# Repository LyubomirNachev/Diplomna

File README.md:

# Diplomna
Проектиране на сензорна IoT мрежа, използваща протокола Thread.

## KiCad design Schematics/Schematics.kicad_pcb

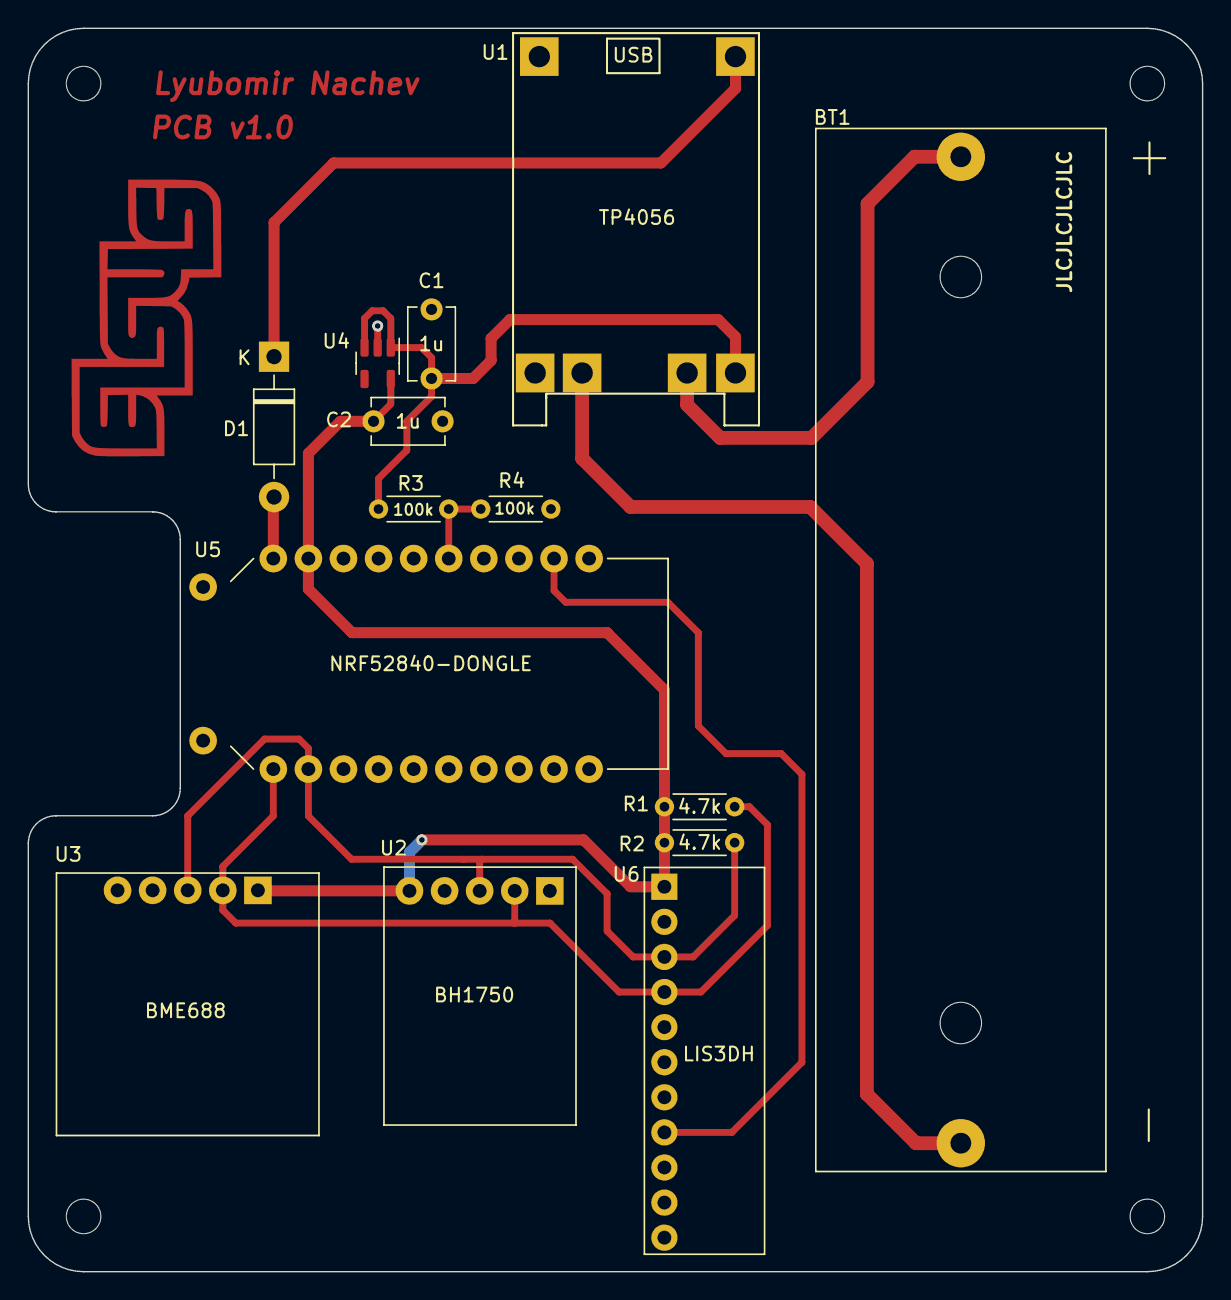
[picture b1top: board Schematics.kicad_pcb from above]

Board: 2 copper layers, 85.0 x 90.0 mm, 19 parts (0 on the bottom side), 11 nets.

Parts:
BT1: 3.7V Li-ion; BHC-18650-1P
C1, C2: 1u; C_Disc_D5.1mm_W3.2mm_P5.00mm
D1: 1N5817; D_DO-41_SOD81_P10.16mm_Horizontal
H1, H2, H3, H4: MountingHole; MountingHole_2.5mm
H5: MountingHole; Slot
R1, R2: 4.7k; R_Axial_DIN0204_L3.6mm_D1.6mm_P5.08mm_Horizontal
R3, R4: 100k; R_Axial_DIN0204_L3.6mm_D1.6mm_P5.08mm_Horizontal
U1: TP4056; TP4056-18650
U2: BH1750
U3: BME688
U4: BU30TD3WG; SOT-23-5
U5: NRF52840-DONGLE; MODULE_NRF52840-DONGLE
U6: LIS3DH

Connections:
+3V0: C2.1, R1.1, R2.2, U2.5 (VCC), U3.1 (2-6V), U4.5 (VOUT), U5.OUT, U6.1 (VCC)
/INT1: U5.1.10, U6.8 (INT1)
/SCL: R2.1, U2.3 (SCL), U3.3 (SCL), U5.0.15, U6.3 (SCL)
/SDA: R1.2, U2.2 (SDA), U3.2 (SDA), U5.0.13, U6.4 (SDA)
GNDD: C1.2, C2.2, R4.1, U1.2 (IN-), U1.6 (OUT-), U2.4 (GND), U3.5 (GND), U4.2 (GND), U5.G1 (GND), U5.G2 (GND), U5.G3 (GND), U6.2 (GND)
unnamed: BT1.1 (+), U1.4 (B+)
unnamed: BT1.2 (-), U1.5 (B-)
unnamed: D1.1 (K), U1.1 (IN+)
unnamed: R3.2, R4.2, U5.0.02
VBUS: D1.2 (A), U5.VBUS
VCC: C1.1, R3.1, U1.3 (OUT+), U4.1 (VIN), U4.3 (STBY)

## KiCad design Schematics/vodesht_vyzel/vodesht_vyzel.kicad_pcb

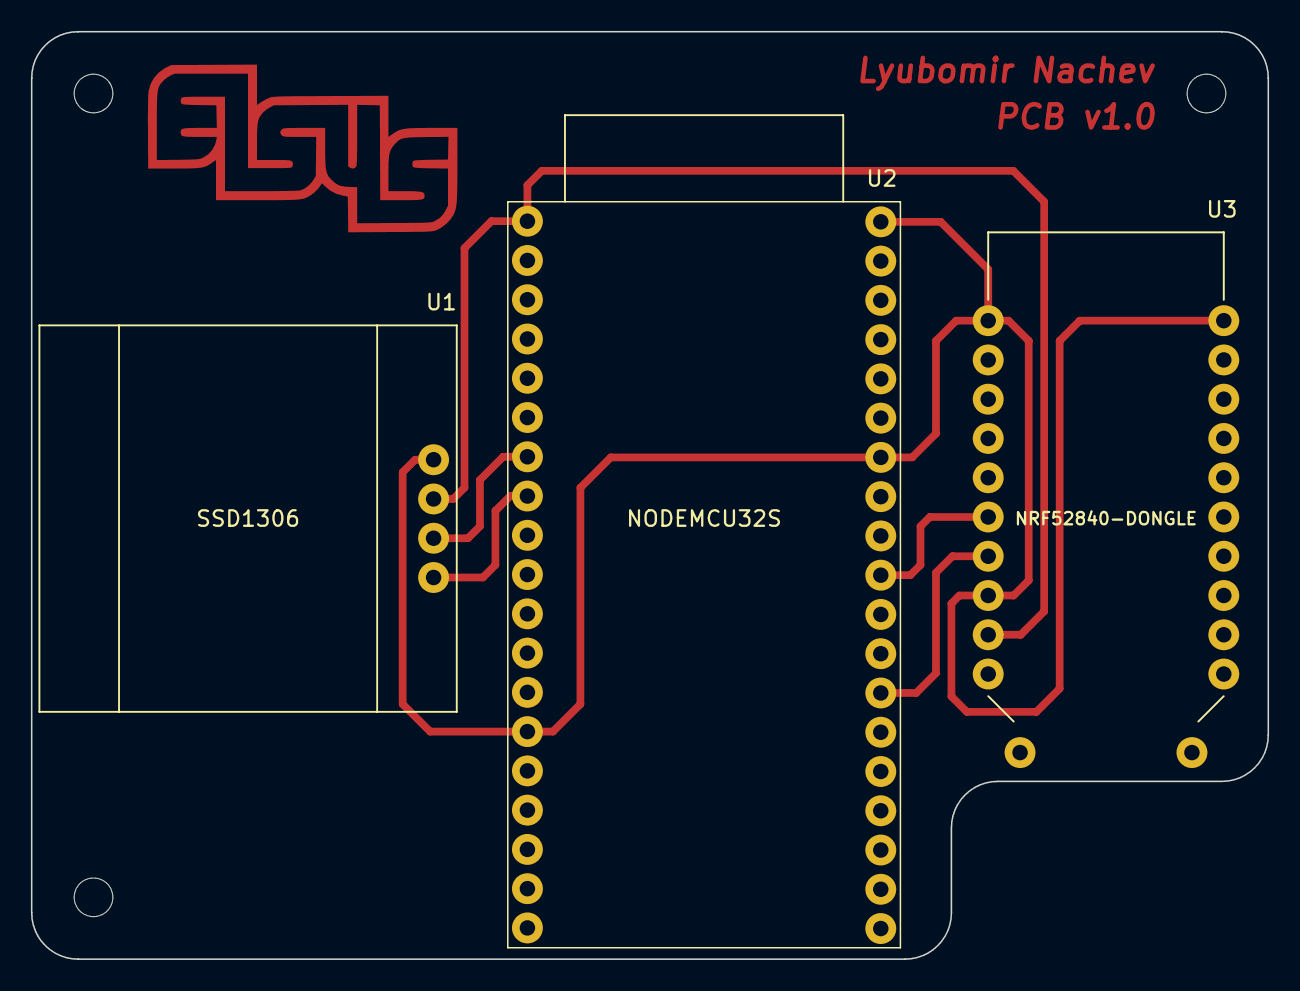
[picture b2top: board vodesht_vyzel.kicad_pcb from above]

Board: 2 copper layers, 80.0 x 60.0 mm, 6 parts (0 on the bottom side), 6 nets.

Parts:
H1, H2, H3: MountingHole; MountingHole_2.5mm
U1: SSD1306; 128x64OLED
U2: NODEMCU32S
U3: NRF52840-DONGLE; MODULE_NRF52840-DONGLE

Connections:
+3.3V: U1.2 (VDD), U2.1 (3V3), U3.14 (OUT)
GNDD: U1.1 (GND), U2.14 (GND), U2.20 (GND), U2.26 (GND), U3.11 (GND), U3.15 (GND), U3.22 (GND)
unnamed: U1.3 (SCL), U2.7 (P32)
unnamed: U1.4 (SDA), U2.8 (P33)
unnamed: U2.29 (P5), U3.17 (0.29)
unnamed: U2.32 (P4), U3.16 (0.31)

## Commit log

2022-12-02 Added .gitignore
2022-12-02 Updated .gitignore
2022-12-02 Test commit
2022-12-04 Changed .gitignore
2022-12-04 Custom sample button program
2022-12-06 Updated .gitignore to add only /apps and /ncs
2022-12-06 Removing folders and fixing .gitignore
2022-12-06 Removing files
2022-12-06 Fixing .gitignore
2022-12-06 Adding test hello world esp example
2022-12-06 Adding nRF52 button test program
2022-12-06 Fixed .gitignore issue
2022-12-19 Tested console example
2022-12-20 Experimented with zephyr's coprocessor example
2022-12-27 Created blinky_thread_cli with custom options(doesn't work), experimented with cli examples and on cli_2 my computer detects the device but no drivers(still in progress)
2022-12-27 Found that example works when configured with console parameter in device tree but with shell-uart doesn't
2022-12-27 Made working usb console that can print
2022-12-27 Tested shell_uart again
2022-12-27 Added copy of isl29035 example to use as base for bh1750 program development
2022-12-27 Fixed .gitignore to track two additional folders
2022-12-27 Added wireshark capture with icmpv6 traffic from the br
2022-12-27 Deleted coprocessor example
2022-12-27 Reuploaded coprocessor example
2022-12-27 Deleted bh1750 and console
2022-12-27 Added bh1750 and console
2022-12-27 Added esp32 ot_br example
2022-12-28 Modified .gitignore, added files, changed bh1750 example
2022-12-28 Added files for future development with bh1750
2022-12-28 Edited configuration
2022-12-30 Added deffinitions in header file
2022-12-31 Edited the bh1750 files
2023-01-01 Major changes for the bh1750 example
2023-01-02 Minor fixes on the bh1750 example
2023-01-02 Fixes for the bh1750 example, added and changed .dtsi file
2023-01-03 Working BH1750 example after fixes
2023-01-06 Created and edited example for lis3dh
2023-01-06 Minor edits on the bh1750 example
2023-01-06 Old examples for bmp280 and bme688
2023-01-07 Added library for lis3dh, made minor changes
2023-01-07 Experimented with cli example, cli_3 is fully working
2023-01-09 Experimented with cli
2023-01-09 Fixed BME688 example (working)
2023-01-09 Added schematics
2023-01-09 Edited schematic
2023-01-14 Added Txpower setting
2023-01-14 Fixed schematic
2023-01-14 Minor changes in the bh1750 (cleanup)
2023-01-15 Cleaned up cli_2 example (working)
2023-01-15 Created and imported footprints for modules
2023-01-15 Created schematic for the leader node
2023-01-18 Changed some footprints and started the pcb development
2023-01-21 Uploading Modified Schematic with PCB version 1
2023-01-21 Uploading 3d models for the components
2023-01-21 Added a second design for a pcb
2023-01-21 Added a third design for a pcb
2023-01-27 Added a couple prototypes for a pcb
2023-01-27 Edited lis3dh library
2023-01-28 Added 3D model and footprint for bhc-18650-1p
2023-01-28 Created new versions of the pcb and generated gerber/drill files
2023-01-28 Added UDP Send message functionality
2023-01-29 Made changes on send example, started work on receive cli example
2023-01-29 Changed sda/scl pins to 0.13 and 0.15
2023-01-30 Added almost(maybe even) finnal design and new gerber and drill files
2023-01-30 Created final variant of the pcb, moved the schematic of the main node in this folder, modified the schematic of the main node
2023-01-30 Deleted the Schematics_vodesht_vyzel folder
2023-01-30 Created working example with esp32 and ssd1306 display module
2023-01-30 Cleaned up some files in the Schematic folder
2023-01-30 Created example for reading battery level
2023-01-31 Generated gerber and bom files
2023-02-01 Edited the pcb board of the vodesht_vyzel and did some small changes on the pcb of the main module
2023-02-03 Fixed some footprints and made changes on the leader node pcb
2023-02-03 Automatic startup and not working code for opening udp port
2023-02-03 Added 3d models for esp32s and ssd1306
2023-02-04 Added automatic udp socket start
2023-02-04 Made small changes in the schematics
2023-02-06 Working http server example
2023-02-06 Working webpage change when a packet is received on the esp border router
2023-02-09 Copied websocket server example from esp-idf
2023-02-10 Data from bh1750 is being successfully send from edge device to the border router
2023-02-10 Edited the example of the ws_echo_eserver and successfully added websocket functionality to the ot_br program
2023-02-10 Made some changes to the bh1750 library so thata it can work on the combined_example
2023-02-10 Working websocket page with value change
2023-02-10 Changes on the vodesht_vyzel pcb and schematics
2023-02-10 Experimented and cleaned up the display example
2023-02-10 Added display functionality to the BR
2023-02-10 Troubleshooting the integration of the bme688 into the combined_work program
2023-02-15 Added bme688 to combined_work and created a custom board
2023-02-15 Changed the pins for the uart0 node
2023-02-15 Created custom board, made functional send after chanign the multicast address to a mesh-local one, made some small changes in other programs and tried adc sample
2023-02-15 Generated new gerber files for the leader_node pcb
2023-02-16 Working adc pin read
2023-02-20 Small changes
2023-02-20 Cleaned up the example
2023-02-26 added software for nrf sniffer and made minor changes on other examples
2023-02-27 Configured ip on display to be gotten automaticly
2023-02-28 Cleaned up the code for the Main node and Leader node and added comments
2023-02-28 Fixed comments on the Leader node
2023-03-05 Final commit
2023-03-05 Uploading documentation
2023-03-13 Final documentation
2023-04-08 Updating stuff
2023-04-09 Websocket updates
2023-04-14 Interface for webpage, hadware id, lis3dh working
2023-04-18 Added led for sending messages, another for just powering on, tested to see that the interrupt is working on the lis3dh and configured somewhat working javascript for the websocket
2023-04-21 Working update of information(still testing tho)
2023-04-21 Added movement detection to the data that is being send
2023-04-21 Working one update of data
2023-04-21 Working live data update
2023-04-21 Little additions
2023-04-21 Fully working websocket with all the devices
